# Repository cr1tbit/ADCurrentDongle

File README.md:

# CurrentDongle attachment for the `Analog Discovery 2`

I actually use this simple board all the time, so decided to share it with the world.

It was made for these reasons:
* Simplifying current consumption measurement process, using AD2 bulit-in programmable voltage source, and dual INA186 amplifiers (for extended dynamic range)
* Breaking out BNC connectors, because, for some reason, such breakout board from Analog costs an ARM and a leg.
* Just breakout board for hacking stuff together

There's an simple bulit-in comparator circuit that blinks a LED when the channel range is reached. The high-accuracy channel usually also blinks when the DUT performs some action, which is also an useful feedback I guess.

In `Calib` folder, there's an example `digilent waveforms` workspace that I use for current measurement (the `software` folder now has a standalone app that replaces it). Some things to note:
* programmable voltage sources on `AD2` are noisy as hell when the current is under a couple of milliamps - hence the resistor in this area. Keep `JP7` closed: without the pre-load, V+ delivers current in ~8 mA bursts at near-zero load (see M8 and M9 in the lab report).
* the voltage offset errors from `INA186`s can be easilly callibrated out, using the provided script.

Measurements, verification and known issues of this revision: [ADCurrentDongle_LabSession](https://github.com/cr1tbit/ADCurrentDongle_LabSession) (lab report).

What this device is NOT:
* Crosstalk-free oscilloscope adapter
* Super accurate, self calibrating current probe
* Lab-ready device

Stuff to improve:
* The LEDs will not work when system is powered by 1.8V - but it's not fixable easily.

## Some pics:

PCB connected to the Analog Discovery 2

PCB render

PCB IRL

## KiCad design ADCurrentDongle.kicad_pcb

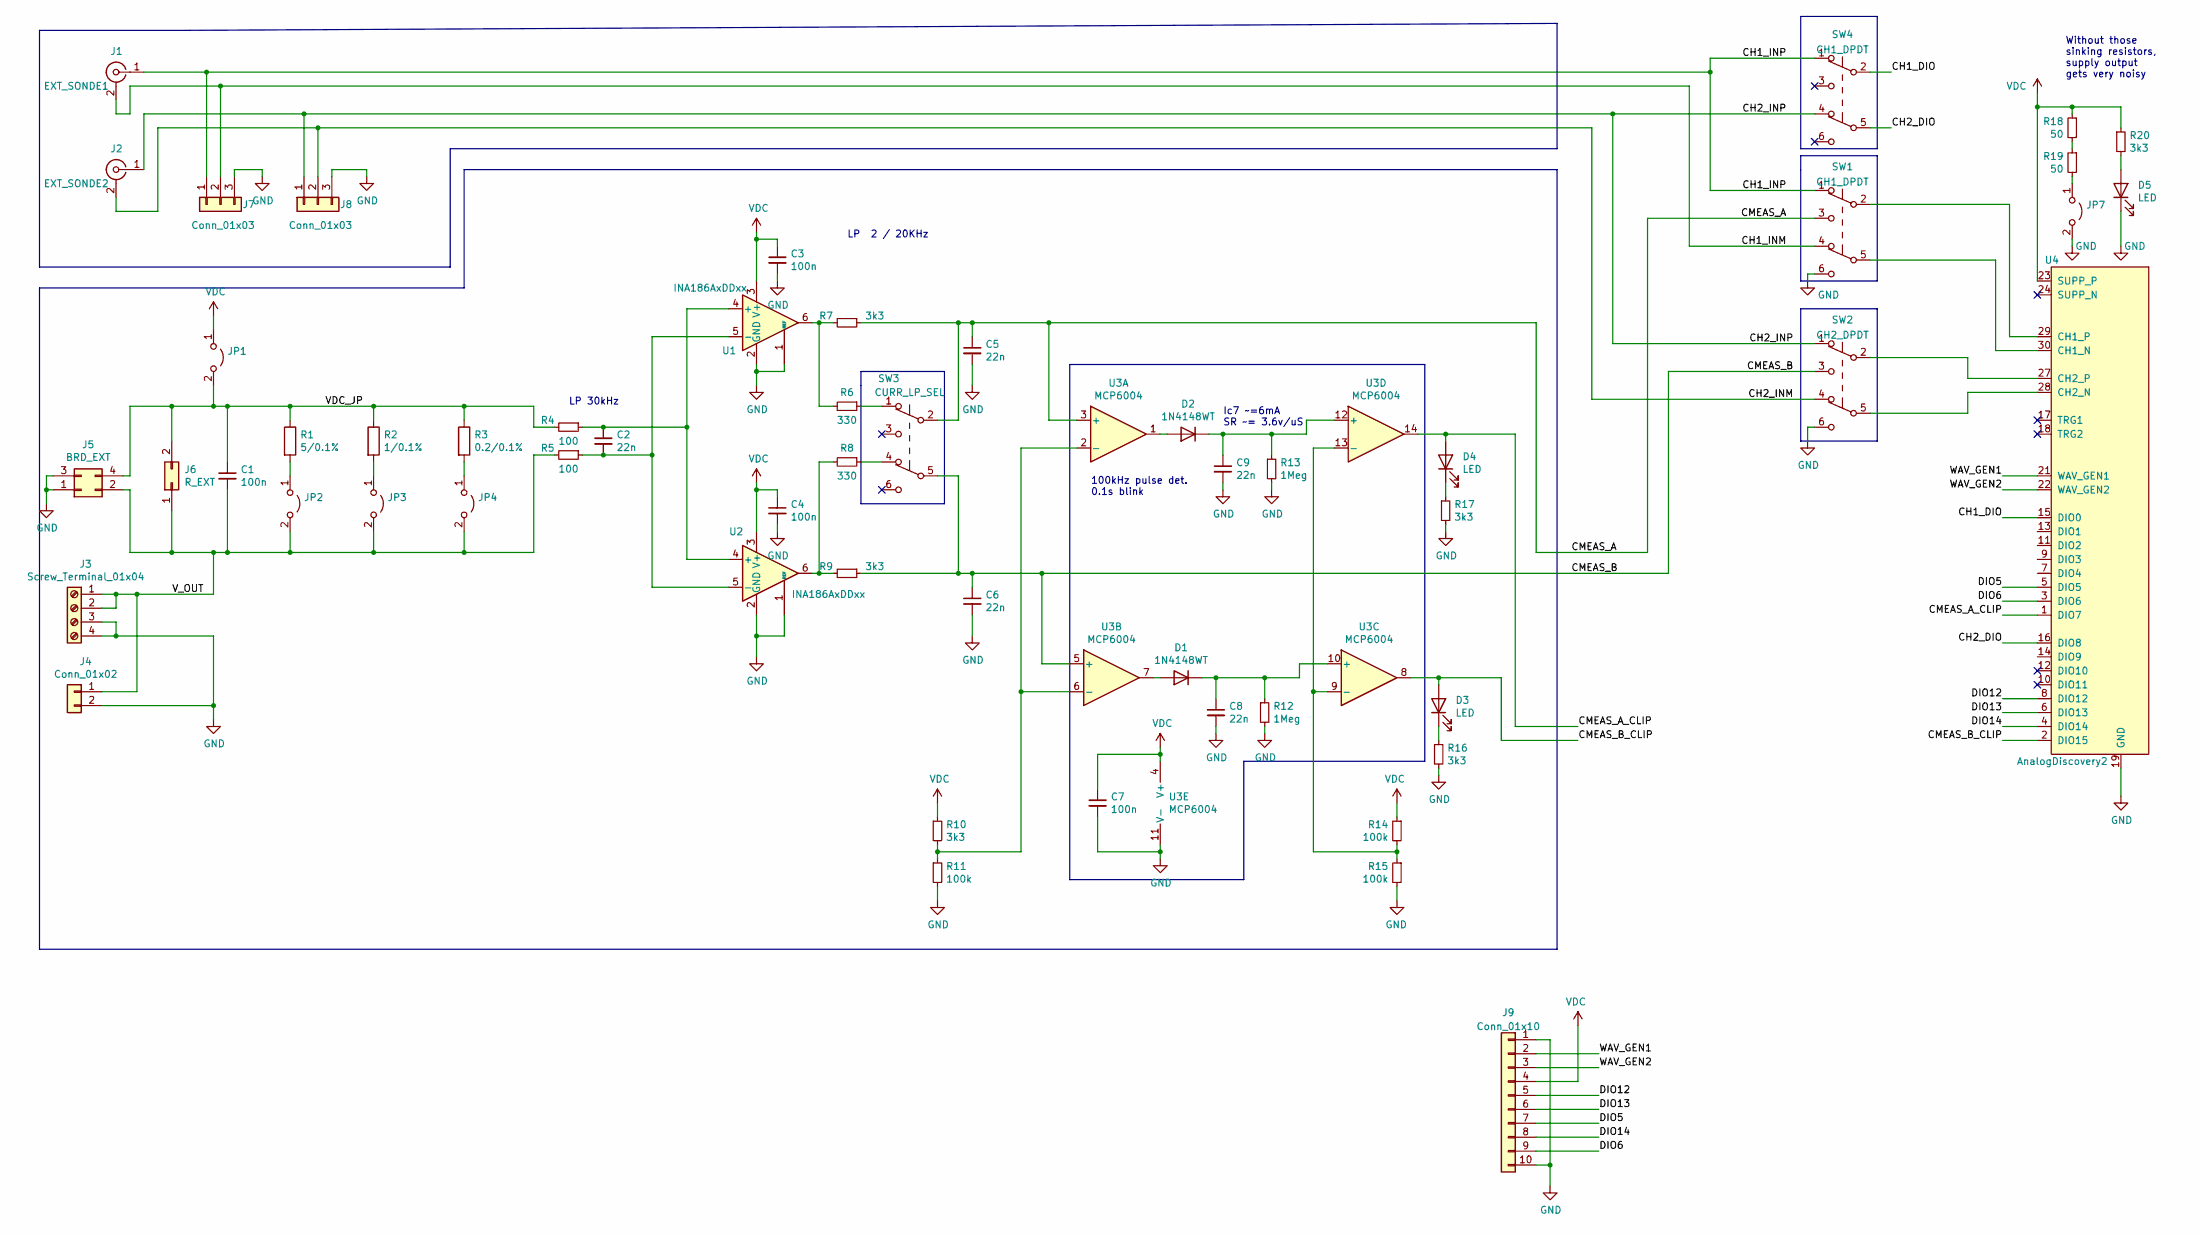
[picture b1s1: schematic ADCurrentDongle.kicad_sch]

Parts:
C1, C3, C4, C7: 100n; C_0402_1005Metric
C2, C5, C6, C8, C9: 22n; C_0402_1005Metric
D1, D2: 1N4148WT; D_SOD-523
D3, D4, D5: LED; LED_0603_1608Metric
J1: EXT_SONDE1; BNC_Amphenol_B6252HB-NPP3G-50_Horizontal
J2: EXT_SONDE2; BNC_Amphenol_B6252HB-NPP3G-50_Horizontal
J3: Screw_Terminal_01x04; TerminalBlock_bornier-4_P5.08mm
J4: Conn_01x02; PinHeader_1x02_P2.54mm_Vertical
J5: BRD_EXT; PinSocket_2x02_P2.54mm_Vertical
J6: R_EXT; PinHeader_1x02_P2.54mm_Vertical
J7, J8: Conn_01x03; PinHeader_1x03_P2.54mm_Vertical
J9: Conn_01x10; PinHeader_1x10_P2.54mm_Vertical
JP1, JP2, JP3, JP4, JP7: Jumper_2_Open; PinHeader_1x02_P2.54mm_Vertical
R1: 5/0.1%; R_1206_3216Metric_Pad1.30x1.75mm_HandSolder
R2: 1/0.1%; R_1206_3216Metric_Pad1.30x1.75mm_HandSolder
R3: 0.2/0.1%; R_1206_3216Metric_Pad1.30x1.75mm_HandSolder
R4, R5: 100; R_0402_1005Metric
R6, R8: 330; R_0402_1005Metric
R7, R9, R10, R16, R17, R20: 3k3; R_0402_1005Metric
R11, R14, R15: 100k; R_0402_1005Metric
R12, R13: 1Meg; R_0402_1005Metric
R18, R19: 50; R_0805_2012Metric
SW1, SW4: CH1_DPDT; SW_DPDT_CK_JS202011JCQN
SW2: CH2_DPDT; SW_DPDT_CK_JS202011JCQN
SW3: CURR_LP_SEL; SW_DPDT_CK_JS202011JCQN
U1, U2: INA186AxDDxx; Texas_R-PDSO-G6
U3: MCP6004; SOIC-14_3.9x8.7mm_P1.27mm
U4: AnalogDiscovery2; AnalogDiscovery2_side_con

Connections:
/CH1_DIO: SW4.2 (B), U4.15 (DIO0)
/CH1_INM: J1.2 (Ext), J7.2, SW1.4 (A)
/CH1_INP: J1.1 (In), J7.1, SW1.1 (A), SW4.1 (A)
/CH2_DIO: SW4.5 (B), U4.16 (DIO8)
/CH2_INM: J2.2 (Ext), J8.2, SW2.4 (A)
/CH2_INP: J2.1 (In), J8.1, SW2.1 (A), SW4.4 (A)
/CMEAS_A: C5.1, R7.1, SW1.3 (C), SW3.2 (B), U3.3 (+)
/CMEAS_A_CLIP: D4.2 (A), U3.14, U4.1 (DIO7)
/CMEAS_B: C6.1, R9.1, SW2.3 (C), SW3.5 (B), U3.5 (+)
/CMEAS_B_CLIP: D3.2 (A), U3.8, U4.2 (DIO15)
/DIO5: J9.7, U4.5 (DIO5)
/DIO6: J9.9, U4.3 (DIO6)
/DIO12: J9.5, U4.8 (DIO12)
/DIO13: J9.6, U4.6 (DIO13)
/DIO14: J9.8, U4.4 (DIO14)
/VDC_JP: C1.1, J5.4, J6.2, JP1.2 (B), R1.1, R2.1, R3.1, R4.2
/V_OUT: C1.2, J3.1, J3.2, J4.1, J5.2, J6.1, JP2.2 (B), JP3.2 (B), JP4.2 (B), R5.2
/WAV_GEN1: J9.2, U4.21 (WAV_GEN1)
/WAV_GEN2: J9.3, U4.22 (WAV_GEN2)
GND: C3.2, C4.2, C5.2, C6.2, C7.2, C8.2, C9.2, D5.1 (K), J3.3, J3.4, J4.2, J5.1, J5.3, J7.3, J8.3, J9.1, J9.10, JP7.2 (B), R11.2, R12.2, R13.2, R15.2, R16.2, R17.2, SW1.6 (C), SW2.6 (C), U1.1 (REF), U1.2 (GND), U2.1 (REF), U2.2 (GND), U3.11 (V-), U4.19 (GND), U4.20 (GND), U4.25 (GND), U4.26 (GND)
unnamed: C2.1, R4.1, U1.4 (+), U2.4 (+)
unnamed: C2.2, R5.1, U1.5 (-), U2.5 (-)
unnamed: C8.1, D1.1 (K), R12.1, U3.10 (+)
unnamed: C9.1, D2.1 (K), R13.1, U3.12 (+)
unnamed: D1.2 (A), U3.7
unnamed: D2.2 (A), U3.1
unnamed: D3.1 (K), R16.1
unnamed: D4.1 (K), R17.1
unnamed: JP2.1 (A), R1.2
unnamed: JP3.1 (A), R2.2
unnamed: JP4.1 (A), R3.2
unnamed: JP7.1 (A), R19.2
unnamed: R6.1, SW3.1 (A)
unnamed: R6.2, R7.2, U1.6
unnamed: R8.1, SW3.4 (A)
unnamed: R8.2, R9.2, U2.6
unnamed: R10.2, R11.1, U3.2 (-), U3.6 (-)
unnamed: R14.2, R15.1, U3.9 (-), U3.13 (-)
unnamed: R18.2, R19.1
unnamed: D5.2 (A), R20.2
unnamed: SW1.2 (B), U4.29 (CH1_P)
unnamed: SW1.5 (B), U4.30 (CH1_N)
unnamed: SW2.2 (B), U4.27 (CH2_P)
unnamed: SW2.5 (B), U4.28 (CH2_N)
VDC: C3.1, C4.1, C7.1, J9.4, JP1.1 (A), R10.1, R14.1, R18.1, R20.1, U1.3 (V+), U2.3 (V+), U3.4 (V+), U4.23 (SUPP_P)

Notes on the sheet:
LP 30kHz
Ic7 ~=6mA SR ~= 3.6v/uS
LP 2 / 20KHz
Without those sinking resistors, supply output gets very noisy
100kHz pulse det. 0.1s blink

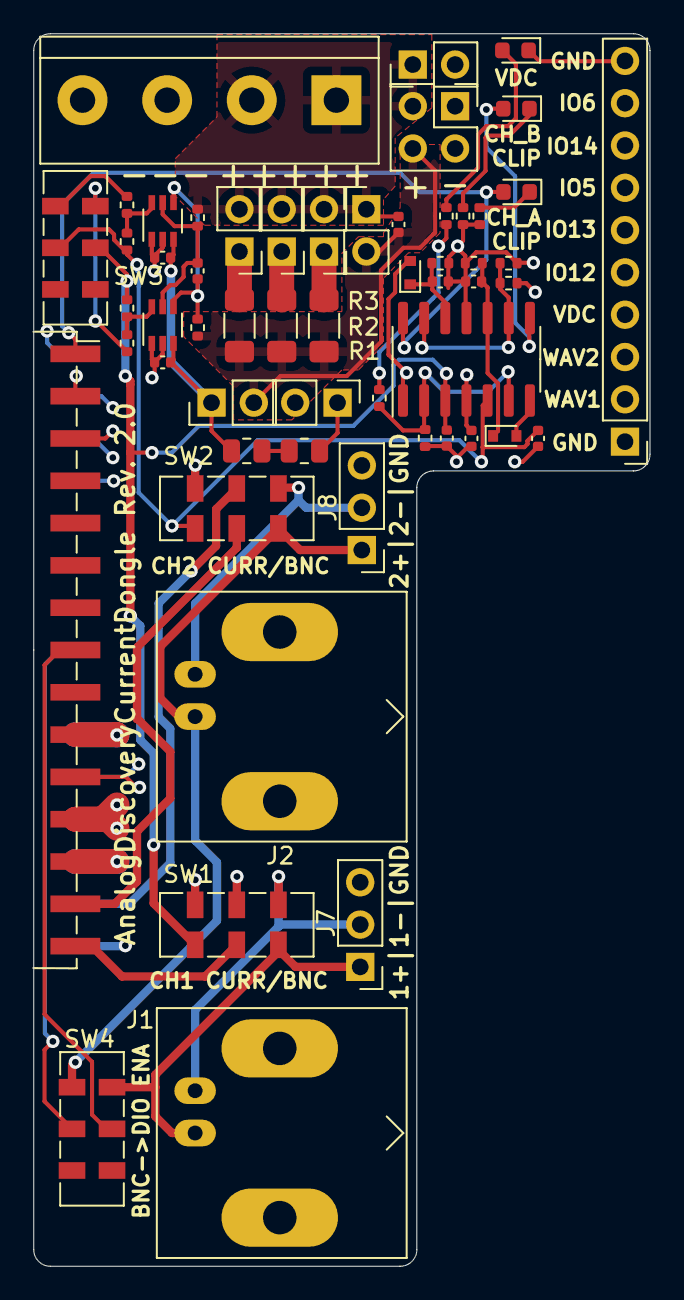
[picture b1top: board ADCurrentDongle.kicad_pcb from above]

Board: 4 copper layers, 37.0 x 74.0 mm, 56 parts (0 on the bottom side), 45 nets.

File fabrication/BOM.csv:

Comment,Designator,Footprint,LCSC
100n,"C1,C3,C4,C7",Capacitor_SMD:C_0402_1005Metric,
22n,"C2,C5,C6,C8,C9",Capacitor_SMD:C_0402_1005Metric,C1532
1N4148WT,"D1,D2",Diode_SMD:D_SOD-523,
LED,"D3,D4,D5",LED_SMD:LED_0603_1608Metric,C2290
5/0.1%,R1,Resistor_SMD:R_1206_3216Metric_Pad1.30x1.75mm_HandSolder,
100k,"R11,R14,R15",Resistor_SMD:R_0402_1005Metric,
1Meg,"R12,R13",Resistor_SMD:R_0402_1005Metric,
50,"R18,R19",Resistor_SMD:R_0805_2012Metric,
1/0.1%,R2,Resistor_SMD:R_1206_3216Metric_Pad1.30x1.75mm_HandSolder,C17928
0.2/0.1%,R3,Resistor_SMD:R_1206_3216Metric_Pad1.30x1.75mm_HandSolder,C25336
100,"R4,R5",Resistor_SMD:R_0402_1005Metric,
330,"R6,R8",Resistor_SMD:R_0402_1005Metric,
3k3,"R7,R9,R10,R16,R17,R20",Resistor_SMD:R_0402_1005Metric,
SWITCHES,"SW1,SW2, SW3, SW4",Button_Switch_SMD:SW_DPDT_CK_JS202011JCQN,C221665
INA186AxDDxx,"U1,U2",Package_TO_SOT_SMD:Texas_R-PDSO-G6,
MCP6004,U3,Package_SO:SOIC-14_3.9x8.7mm_P1.27mm,

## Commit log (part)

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2021-06-25 gityfying the repo
2021-06-25 increasing readability
2021-06-26 renaming project
2022-02-27 commiting WIP in hope of catching a routing bug
2022-03-11 adding new rev fabrication and stuff
2022-05-20 pre order commit
2022-05-23 fabrication outputs
2022-06-23 adding new photos
2022-06-23 fix order of pictures
